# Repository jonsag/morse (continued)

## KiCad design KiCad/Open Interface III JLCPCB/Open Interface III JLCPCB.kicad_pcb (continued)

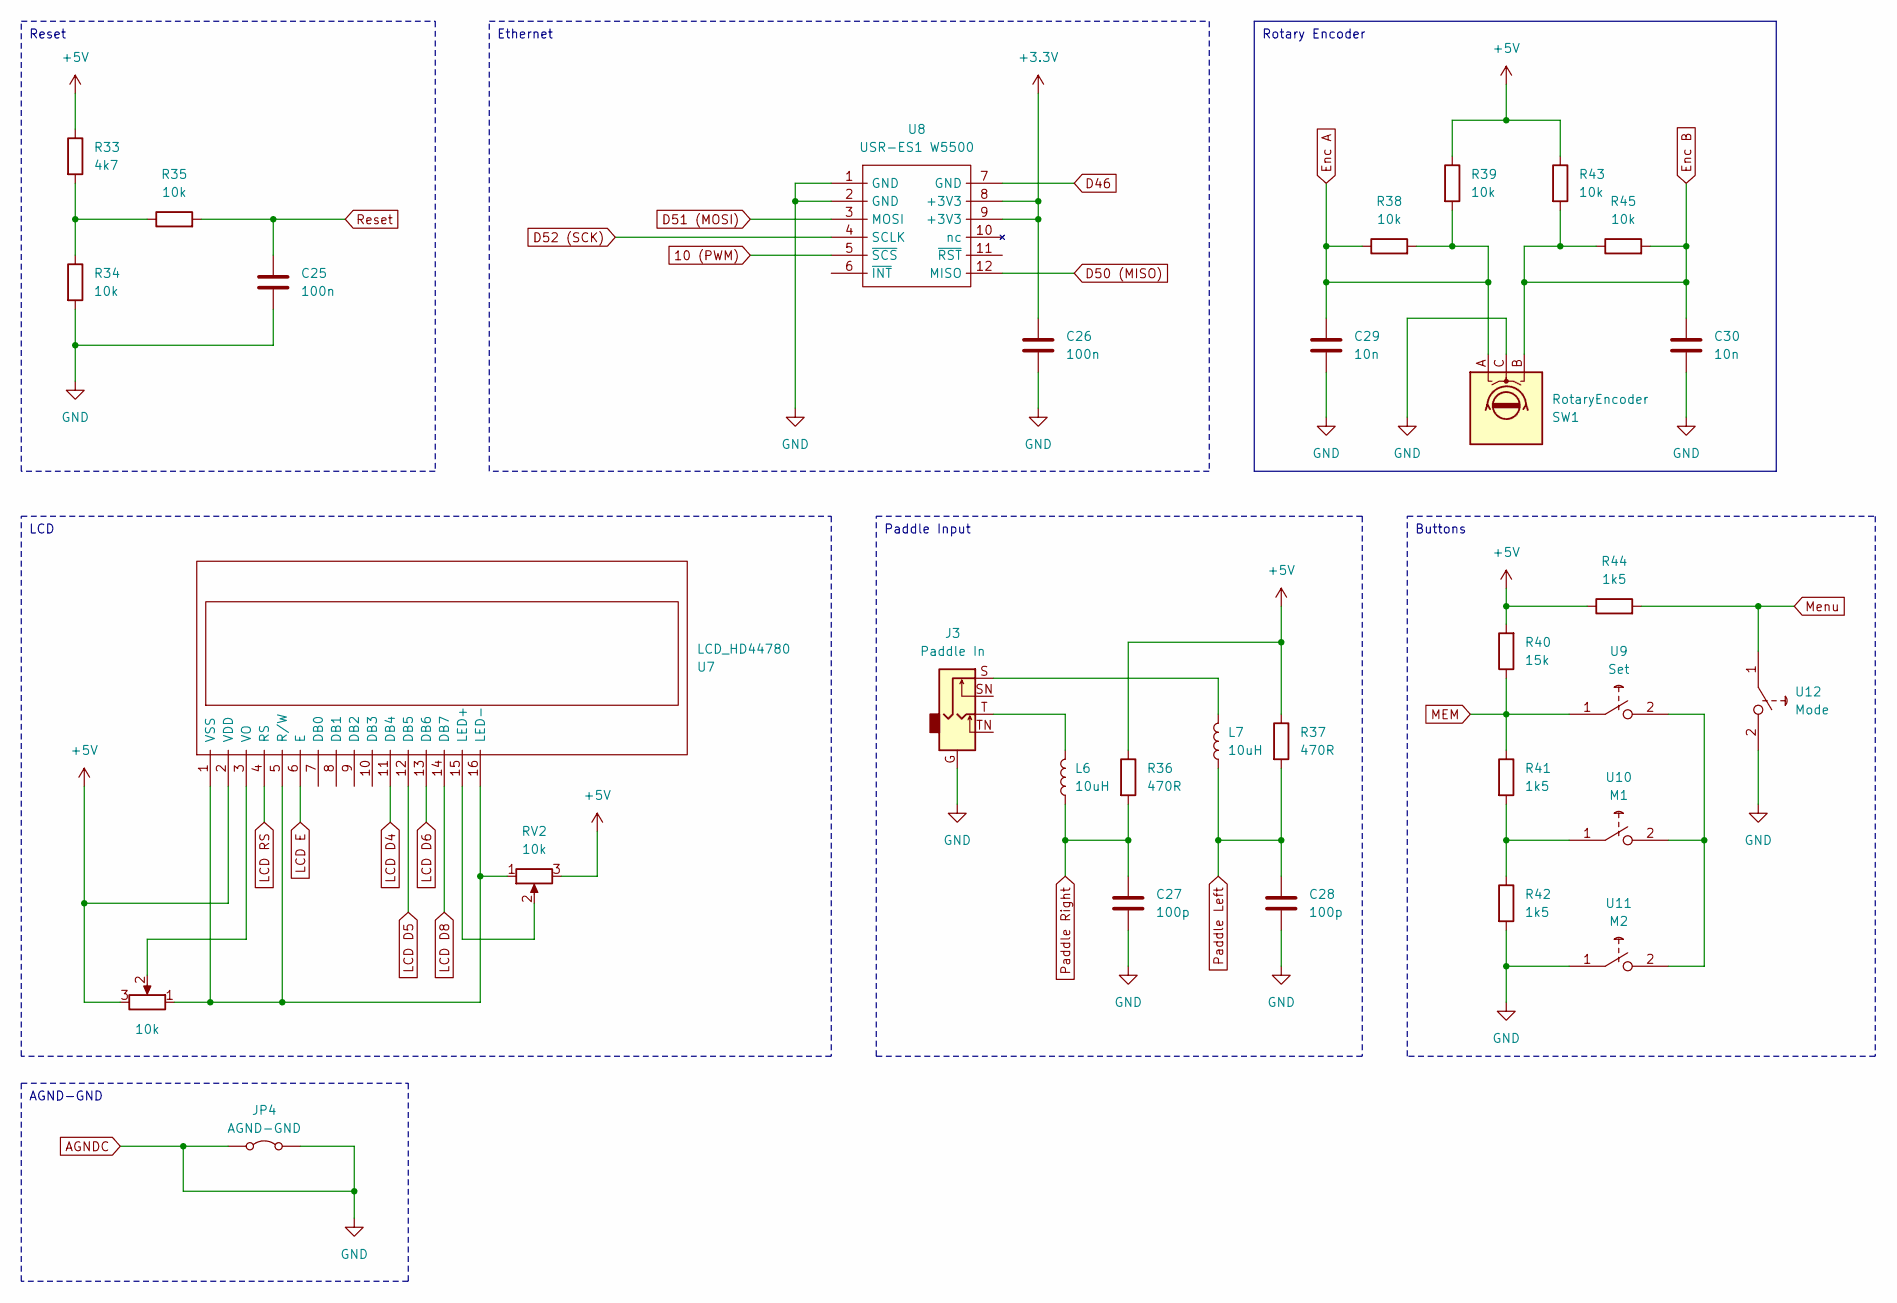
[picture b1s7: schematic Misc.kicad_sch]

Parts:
C25, C26: 100n; C_0201_0603Metric; MPN C1590
C27, C28: 100p; C_0201_0603Metric; MPN C1635
C29, C30: 10n; C_0201_0603Metric; MPN C1589
J3: Paddle In; 3,5mm Jack Panel Socket 3-pole Switch large
JP4: AGND-GND; PinHeader_1x02_P2.54mm_Vertical
L6, L7: 10uH; L_0201_0603Metric; MPN C1035
R33: 4k7; R_0201_0603Metric; MPN C23162
R34, R35, R38, R39, R43, R45: 10k; R_0201_0603Metric; MPN C15401
R36, R37: 470R; R_0201_0603Metric; MPN C23179
R40: 15k; R_0201_0603Metric; MPN C22809
R41, R42, R44: 1k5; R_0201_0603Metric; MPN C22843
RV1, RV2: 10k; 3-pin JST Potentiometer
SW1: RotaryEncoder; 3-pin JST Rotary Encoder
U7: LCD_HD44780; 2 x 6-pin JST LCD HD44780 Stacked
U8: USR-ES1 W5500
U9: Set; 2-pin JST Switch
U10: M1; 2-pin JST Switch
U11: M2; 2-pin JST Switch
U12: Mode; 2-pin JST Switch

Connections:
10 (PWM): U8.5 (~SCS); also elsewhere on the board
+3.3V: C26.1, U8.8 (+3V3), U8.9 (+3V3); also elsewhere on the board
+5V: R33.1, R36.1, R37.1, R39.1, R40.2, R43.1, R44.1, RV1.3, RV2.3, U7.2 (VDD); also elsewhere on the board
AGNDC: C25.2, C26.2, C27.2, C28.2, C29.2, C30.2, J3.G, JP4.1 (A), JP4.2 (B), R34.2, R42.2, SW1.C, U8.1 (GND), U8.2 (GND), U11.1 (Com), U12.2 (NO); also elsewhere on the board
D46: U8.7 (GND); also elsewhere on the board
D50 (MISO): U8.12 (MISO); also elsewhere on the board
D51 (MOSI): U8.3 (MOSI); also elsewhere on the board
D52 (SCK): U8.4 (SCLK); also elsewhere on the board
DTR: C25.1, R35.2; also elsewhere on the board
Enc A: C29.1, R38.1, R38.2, R39.2, SW1.A; also elsewhere on the board
Enc B: C30.1, R43.2, R45.1, R45.2, SW1.B
LCD D4: U7.11 (DB4); also elsewhere on the board
LCD D5: U7.12 (DB5); also elsewhere on the board
LCD D6: U7.13 (DB6); also elsewhere on the board
LCD D8: U7.14 (DB7)
LCD E: U7.6 (E); also elsewhere on the board
LCD RS: U7.4 (RS); also elsewhere on the board
MEM: R40.1, R41.1, U9.1 (Com)
Menu: R44.2, U12.1 (Com); also elsewhere on the board
unnamed: J3.S, L7.2
unnamed: J3.T, L6.2
unnamed: R33.2, R34.1, R35.1
unnamed: RV2.2, U7.15 (LED+)
unnamed: RV1.1, RV2.1, U7.1 (VSS), U7.5 (R/W), U7.16 (LED-)
unnamed: RV1.2, U7.3 (VO)
unnamed: R41.2, R42.1, U10.1 (Com)
unnamed: U9.2 (NO), U10.2 (NO), U11.2 (NO)
Paddle Left: C28.1, L7.1, R37.2; also elsewhere on the board
Paddle Right: C27.1, L6.1, R36.2; also elsewhere on the board

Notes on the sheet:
Paddle Input
Buttons
AGND-GND
Ethernet
LCD
Reset
Rotary Encoder

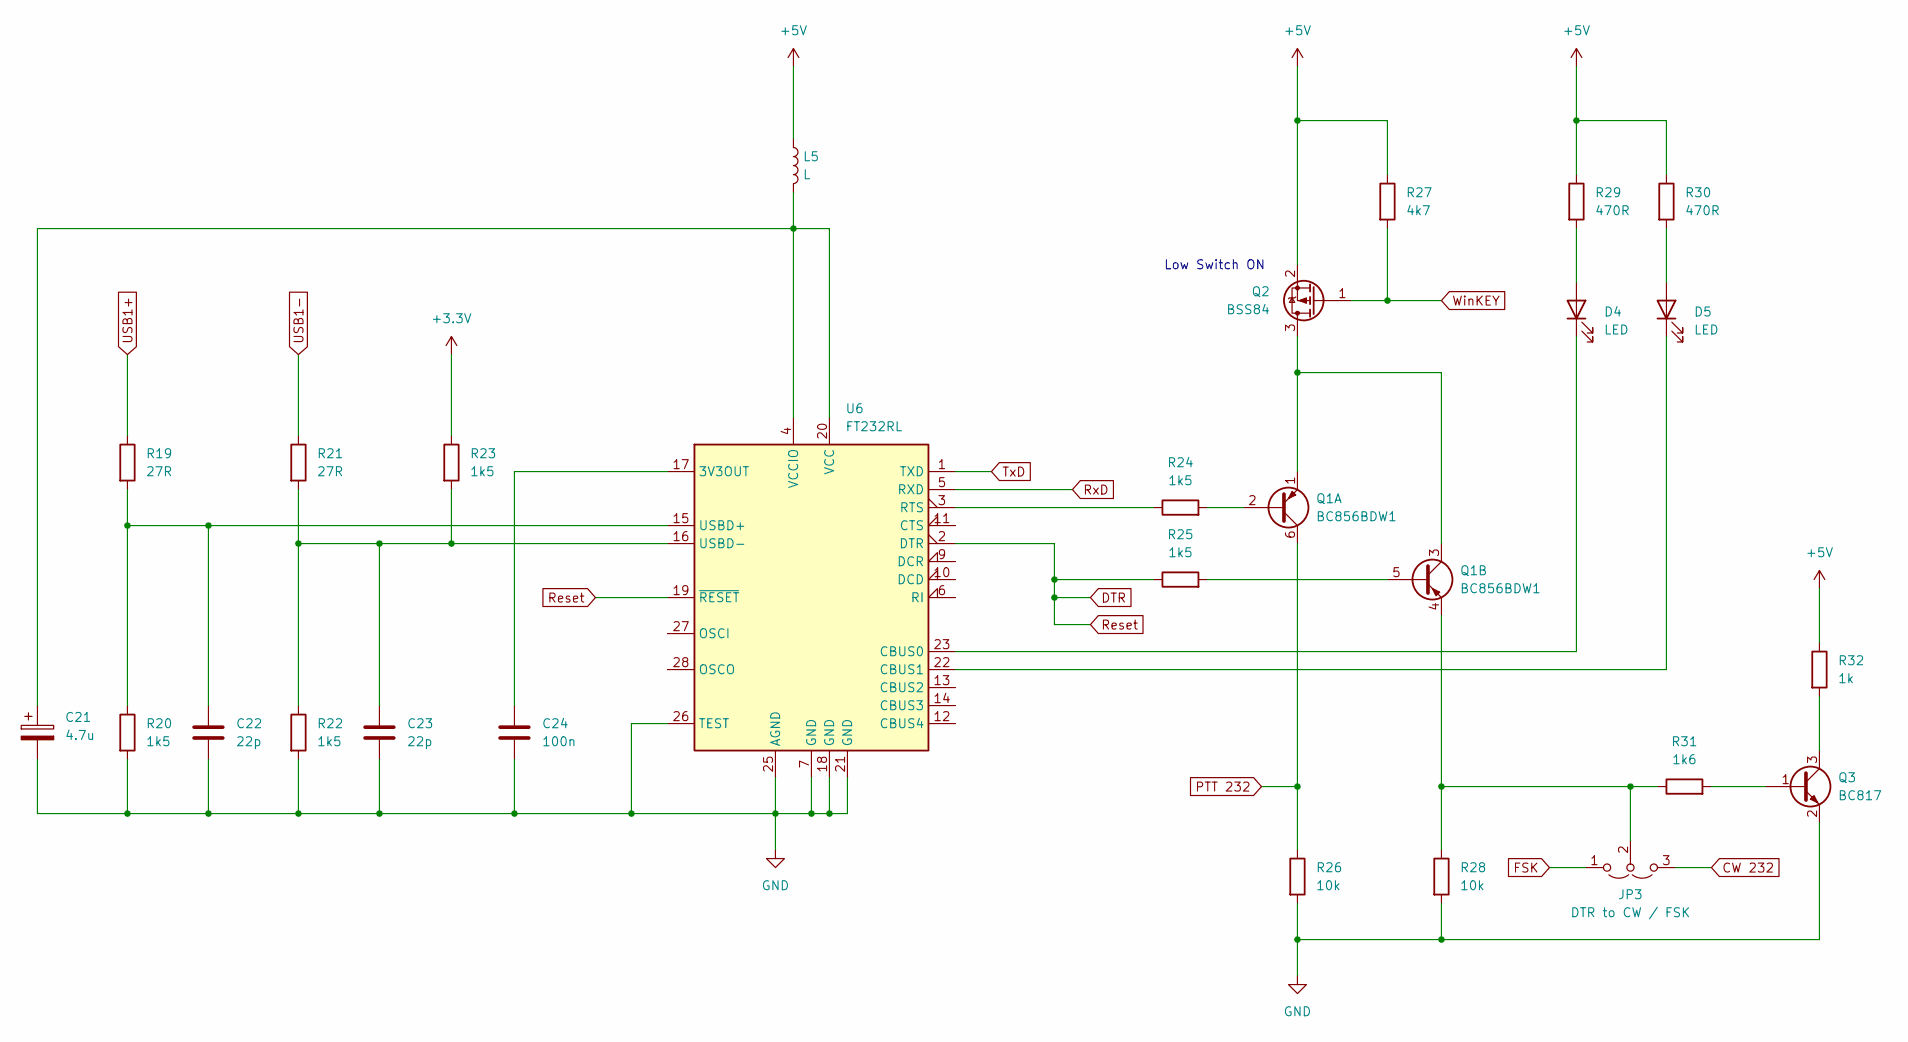
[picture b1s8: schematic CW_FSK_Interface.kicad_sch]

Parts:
C21: 4.7u; CP_Elec_5x5.4; MPN C4747957
C22, C23: 22p; C_0201_0603Metric; MPN C1653
C24: 100n; C_0201_0603Metric; MPN C1590
D4, D5: LED; 2-pin JST LED
JP3: DTR to CW / FSK; Jumper_1x03_P2.54mm_large
L5: L; L_1206_3216Metric_Pad1.22x1.90mm_HandSolder
Q1: BC856BDW1; SOT-363_SC-70-6; MPN C383196
Q2: BSS84; SOT-23; MPN C8492
Q3: BC817; SOT-23-3; MPN C2137
R19, R21: 27R; R_0201_0603Metric; MPN C25190
R20, R22, R23, R24, R25: 1k5; R_0201_0603Metric; MPN C22843
R26, R28: 10k; R_0201_0603Metric; MPN C15401
R27: 4k7; R_0201_0603Metric; MPN C23162
R29, R30: 470R; R_0201_0603Metric; MPN C23179
R31: 1k6; R_0201_0603Metric; MPN C22847
R32: 1k; R_0201_0603Metric; MPN C14676
U6: FT232RL; SSOP-28_5.3x10.2mm_P0.65mm

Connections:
+3.3V: R23.1; also elsewhere on the board
+5V: L5.1, Q2.2 (S), R27.1, R29.1, R30.1, R32.1; also elsewhere on the board
AGNDC: C21.2, C22.2, C23.2, C24.2, Q3.2 (E), R20.2, R22.2, R26.2, R28.2, U6.7 (GND), U6.18 (GND), U6.21 (GND), U6.25 (AGND), U6.26 (TEST); also elsewhere on the board
CW 232: JP3.3 (B); also elsewhere on the board
DTR: R25.1, U6.2 (DTR), U6.19 (~RESET); also elsewhere on the board
FSK: JP3.1 (A); also elsewhere on the board
unnamed: D4.2 (A), R29.2
unnamed: D4.1 (K), U6.23 (CBUS0)
unnamed: D5.2 (A), R30.2
unnamed: D5.1 (K), U6.22 (CBUS1)
unnamed: JP3.2 (C), Q1.4 (E2), R28.1, R31.1
unnamed: Q1.2 (B1), R24.2
unnamed: Q1.1 (E1), Q1.3 (C2), Q2.3 (D)
unnamed: Q1.5 (B2), R25.2
unnamed: Q3.1 (B), R31.2
unnamed: Q3.3 (C), R32.2
unnamed: C24.1, U6.17 (3V3OUT)
unnamed: R24.1, U6.3 (RTS)
unnamed: C22.1, R19.2, R20.1, U6.15 (USBD+)
unnamed: C23.1, R21.2, R22.1, R23.2, U6.16 (USBD-)
unnamed: C21.1, L5.2, U6.4 (VCCIO), U6.20 (VCC)
PTT 232: Q1.6 (C1), R26.1; also elsewhere on the board
RxD: U6.5 (RXD); also elsewhere on the board
TxD: U6.1 (TXD); also elsewhere on the board
USB1+: R19.1; also elsewhere on the board
USB1-: R21.1; also elsewhere on the board
WinKEY: Q2.1 (G), R27.2; also elsewhere on the board

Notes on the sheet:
Low Switch ON

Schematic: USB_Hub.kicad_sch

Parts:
C17, C18: 22p; C_0201_0603Metric; MPN C1653
C19, C20: 27p; C_0201_0603Metric; MPN C1656
R14, R15: 24R; R_0201_0603Metric; MPN C4198
R16, R17: 1k5; R_0201_0603Metric; MPN C22843
R18: 1M; R_0201_0603Metric; MPN C22935
U5: TUSB2046B; LQFP-32_7x7mm_P0.8mm
Y2: 6MHz; Crystal_SMD_HC49-SD; MPN C29835

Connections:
+3.3V: U5.3 (VCC), U5.10 (~OVRCUR1), U5.14 (~OVRCUR2), U5.18 (~OVRCUR3), U5.22 (~OVERCUR4), U5.25 (VCC), U5.26 (~EXTMEM); also elsewhere on the board
AGNDC: C17.2, C18.2, C19.2, C20.2, R16.2, U5.6 (EEDATA/~GANGED), U5.7 (GND), U5.8 (~BUSPWR), U5.27 (TSTPLL/48MCLK), U5.28 (GND), U5.31 (TSTMODE); also elsewhere on the board
DTR: U5.4 (~RESET); also elsewhere on the board
HUB+: R15.1
HUB-: R14.1
unnamed: C19.1, R17.1, R18.1, Y2.1
unnamed: C18.1, R15.2, U5.2 (DM0)
unnamed: C17.1, R14.2, R16.1, U5.1 (DP0)
unnamed: C20.1, R18.2, U5.30 (XTAL1), Y2.2
unnamed: R17.2, U5.29 (XTAL2)
USB1+: U5.12 (DP1); also elsewhere on the board
USB1-: U5.11 (DM1); also elsewhere on the board
USB2+: U5.16 (DP2); also elsewhere on the board
USB2-: U5.15 (DM2); also elsewhere on the board
USB3+: U5.20 (DP3); also elsewhere on the board
USB3-: U5.19 (DM3); also elsewhere on the board
USB4+: U5.24 (DP4); also elsewhere on the board
USB4-: U5.23 (DM4); also elsewhere on the board

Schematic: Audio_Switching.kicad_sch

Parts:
C83, C84, C85, C86: 4.7n; C_0201_0603Metric; MPN C1621
C87: 10u; CP_Elec_4x5.4; MPN C2029
D35, D36: 1N4148; D_SOD-523
J9: Mic In; 3,5mm Jack Panel Socket 3-pole Switch large
JP7: DC to Mic; PinHeader_1x02_P2.54mm_Vertical
K2, K3: G5V-1; Relay_SPDT_Omron_G5V-1
L28, L29, L30, L31: 10uH; L_0201_0603Metric; MPN C1035
Q5: BC817; SOT-23-3; MPN C2137
Q6: BC856B; SOT-23-3; MPN C85077
R83: 10k; R_0201_0603Metric; MPN C15401
R84, R85: 1k5; R_0201_0603Metric; MPN C22843
RV5: 10k; 3-pin JST Potentiometer
U24, U25: 2 x RCA Jack; pro-signal PSG01550 Dual 2× RCA Phono SocketRight Angle PCB

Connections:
+5V: D35.1 (K), D36.1 (K), K2.2, K3.2, R83.1; also elsewhere on the board
AFSK: R85.1; also elsewhere on the board
AGNDC: C83.2, C84.2, C85.2, C86.2, Q5.2 (E), Q6.3 (C), U24.1, U25.1; also elsewhere on the board
Interlock In: C84.1, L29.1; also elsewhere on the board
Mic Out: K3.5, K3.6; also elsewhere on the board
unnamed: D35.2 (A), K2.9, Q5.3 (C)
unnamed: D36.2 (A), K3.9, Q6.2 (E)
unnamed: C87.2, JP7.1 (A), K3.10
unnamed: C87.1, J9.T, JP7.2 (B)
unnamed: K2.1, RV5.3
unnamed: K3.1, RV5.2
unnamed: L28.1, U24.3
unnamed: L29.2, U25.2
unnamed: L30.2, U25.3
unnamed: L31.1, U24.2
unnamed: Q5.1 (B), R85.2
unnamed: Q6.1 (B), R84.2
PA PTT Out: C85.1, L30.1; also elsewhere on the board
PTT from Foot: C86.1, L31.2, R83.2, R84.1; also elsewhere on the board
SEQ Out: C83.1, L28.2; also elsewhere on the board
Tx Audio: K2.10
Tx Audio GND: J9.G, RV5.1; also elsewhere on the board
Tx Sound: K2.5, K2.6; also elsewhere on the board

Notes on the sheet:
Sequencer
Foot PTT
PA PTT
Interlock In

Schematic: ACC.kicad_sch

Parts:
J10: UART; PinHeader_1x03_P2.54mm_Vertical
J11: HDMI_A; HDMI_A_Kycon_KDMIX-SL1-NS-WS-B15_VerticalRightAngle

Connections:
+5V: J11.18 (+5V); also elsewhere on the board
A3: J11.12 (CK-); also elsewhere on the board
A4: J11.13 (CEC); also elsewhere on the board
A8: J11.14 (UTILITY); also elsewhere on the board
A9: J11.17 (GND); also elsewhere on the board
A11: J11.19 (HPD); also elsewhere on the board
AGNDC: J10.3, J11.2 (D2S), J11.SH; also elsewhere on the board
D5: J11.6 (D1-); also elsewhere on the board
D11: J11.9 (D0-); also elsewhere on the board
D12: J11.10 (CK+); also elsewhere on the board
D13: J11.5 (D1S); also elsewhere on the board
D30: J11.7 (D0+); also elsewhere on the board
D32: J11.8 (D0S); also elsewhere on the board
D38: J11.11 (CKS); also elsewhere on the board
D47: J11.4 (D1+); also elsewhere on the board
RxD3: J10.1, J11.1 (D2+); also elsewhere on the board
SCL: J11.15 (SCL); also elsewhere on the board
SDA: J11.16 (SDA); also elsewhere on the board
TxD3: J10.2, J11.3 (D2-); also elsewhere on the board

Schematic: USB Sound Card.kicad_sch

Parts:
C59, C62, C65, C66, C77, C79: 10u; CP_Elec_4x5.4; MPN C2029
C60, C61, C78, C80: 22p; C_0201_0603Metric; MPN C1653
C63: 100n; C_0201_0603Metric; MPN C1590
C64: 47u; CP_Elec_5x5.4; MPN C3337
C67, C71, C72, C75, C81, C82: 1u; CP_Elec_4x5.4; MPN C3348
C68, C74: 1n; C_0201_0603Metric; MPN C1588
C69, C73: 10u; C_0201_0603Metric; MPN C1691
C70: 68n; C_0201_0603Metric; MPN C31658
C76: 4.7u; CP_Elec_5x5.4; MPN C4747957
D31, D32, D33, D34: 1N4148; D_SOD-523
L27: L; L_1206_3216Metric_Pad1.22x1.90mm_HandSolder
Q4: BC817; SOT-23-3; MPN C2137
R67, R71: 27R; R_0201_0603Metric; MPN C25190
R68, R76, R77, R78, R82: 4k7; R_0201_0603Metric; MPN C23162
R69, R75: 100k; R_0201_0603Metric; MPN C14675
R70, R79: 470R; R_0201_0603Metric; MPN C23179
R72, R74: 15k; R_0201_0603Metric; MPN C22809
R73: 1k5; R_0201_0603Metric; MPN C22843
R80: 1k; R_0201_0603Metric; MPN C14676
R81: 1M; R_0201_0603Metric; MPN C22935
RV4: 10k log; 3-pin JST Potentiometer
T1, T2: Transformer_1P_1S; Audio Transformer Bourns SM-LP-5001; MPN C7503474
U20: Vol -; 2-pin JST Switch
U21: Vol +; 2-pin JST Switch
U22: Mute; 2-pin JST Switch
U23: PCM2904; SSOP-28_5.3x10.2mm_P0.65mm
Y3: 12 MHz; Crystal_SMD_HC49-SD

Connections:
+3.3V: R73.1; also elsewhere on the board
+5V: L27.1; also elsewhere on the board
AGNDC: C60.2, C61.2, C63.2, C64.2, C67.2, C71.2, C72.2, C75.2, C76.2, C77.2, C78.2, C80.2, C82.2, D32.1 (K), D34.2 (A), R70.2, R72.1, R74.1, R75.2, U23.4 (DGNDU), U23.11 (AGNDC), U23.18 (AGNDP), U23.22 (AGNDX), U23.24 (TEST0), U23.26 (DGND); also elsewhere on the board
unnamed: C63.1, R68.2
unnamed: C66.2, RV4.2
unnamed: C73.1, R79.2
unnamed: C79.2, C81.2, R82.2
unnamed: C59.2, C62.2, C65.2, D31.2 (A), D33.1 (K)
unnamed: D31.1 (K), D32.2 (A)
unnamed: D33.2 (A), D34.1 (K)
unnamed: C66.1, Q4.1 (B), R69.2, R75.1
unnamed: C59.1, Q4.3 (C), R68.1, R69.1
unnamed: C64.1, Q4.2 (E), R70.1
unnamed: RV4.1, T1.1 (AA)
unnamed: RV4.3, T1.2 (AB)
unnamed: C69.2, T1.4 (SB)
unnamed: C73.2, T2.1 (AA)
unnamed: C74.2, T2.2 (AB)
unnamed: R80.1, R82.1, T2.4 (SB)
unnamed: R76.2, U20.1 (Com)
unnamed: U20.2 (NO), U23.7 (HID2)
unnamed: R77.2, U21.1 (Com)
unnamed: U21.2 (NO), U23.6 (HID1)
unnamed: R78.2, U22.1 (Com)
unnamed: U22.2 (NO), U23.5 (HID0)
unnamed: R71.2, R73.2, R74.2, U23.1 (D+)
unnamed: R67.2, R72.2, U23.2 (D-)
unnamed: C67.1, U23.8 (SEL0), U23.9 (SEL1), U23.27 (VDDI)
unnamed: C82.1, L27.2, U23.3 (VBUS)
unnamed: C77.1, U23.10 (VCCCI)
unnamed: C75.1, U23.17 (VCCP1I)
unnamed: C72.1, U23.19 (VCCP2I)
unnamed: C71.1, U23.23 (VCCXI)
unnamed: C76.1, U23.14 (VCOM)
unnamed: C65.1, U23.12 (VINL)
unnamed: C62.1, U23.13 (VINR)
unnamed: C79.1, U23.16 (VOUTL)
unnamed: C81.1, U23.15 (VOUTR)
unnamed: C80.1, R81.2, U23.21 (XTI), Y3.2
unnamed: C78.1, R81.1, U23.20 (XTO), Y3.1
unnamed: R76.1, R77.1, R78.1, U23.28 (~SSPND)
Rx Audio: C68.1, C69.1
Rx Audio GND: C68.2, T1.3 (SA)
Tx Audio GND: C70.2, C74.1; also elsewhere on the board
Tx Sound: C70.1, R79.1; also elsewhere on the board
USB3+: C61.1, R71.1; also elsewhere on the board
USB3-: C60.1, R67.1; also elsewhere on the board
VGNDC: R80.2, T2.3 (SA)

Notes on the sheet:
Option

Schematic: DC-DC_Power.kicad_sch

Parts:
C36: 100u; CP_Elec_6.3x7.7; MPN C3338
C37, C38, C39, C42: 100n; C_0201_0603Metric; MPN C1590
C40, C41: 10u; CP_Elec_4x5.4; MPN C2029
C43: 1000u; CP_Elec_8x10.5; MPN C42851
D6, D7, D8: SK38; D_SMB; MPN C28646291
J7: Barrel_Jack_Switch; BarrelJack_Horizontal
L24, L25: 100uH; L_SXN_SMDRI124; MPN C10150
RV3: 18VDC; RV_Disc_D12mm_W3.9mm_P7.5mm
U15: LM2576HVS-5; TO-263-5_TabPin6; MPN LM2576HVS-5
U16: L78L33_SOT89; SOT-89-3; MPN C14170

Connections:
+3.3V: C41.1, C42.1, U16.1 (OUT); also elsewhere on the board
+5V: C37.1, C39.1, C40.1, C43.1, L25.2, U15.4 (FB), U16.3 (IN); also elsewhere on the board
AGNDC: C36.2, C37.2, C38.2, C39.2, C40.2, C41.2, C42.2, C43.2, D8.2 (A), J7.2, RV3.2, U15.3 (GND), U15.5 (~ON/OFF), U16.2 (GND); also elsewhere on the board
unnamed: D6.1 (K), D7.1 (K), L24.1
unnamed: D7.2 (A), J7.1
unnamed: D8.1 (K), L25.1, U15.2 (OUT)
Vin: C36.1, C38.1, L24.2, RV3.1, U15.1 (VIN); also elsewhere on the board
Vin TRX: D6.2 (A); also elsewhere on the board

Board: 2 copper layers, 302 parts (0 on the bottom side), 257 nets, no tracks yet.

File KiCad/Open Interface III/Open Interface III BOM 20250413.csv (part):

"Reference","Value","Datasheet","Footprint","Qty","DNP"
"C1,C4,C8,C17,C18,C22,C23,C31,C32,C33,C53,C54,C60,C61,C78,C80","22p","~","Capacitor_SMD:C_1206_3216Metric_Pad1.33x1.80mm_HandSolder","16",""
"C2,C3,C5,C9,C44,C45,C47,C49,C83,C84,C85,C86","4.7n","~","Capacitor_SMD:C_1206_3216Metric_Pad1.33x1.80mm_HandSolder","12",""
"C6,C7,C10,C11,C12,C13,C14,C15,C16,C24,C25,C26,C34,C35,C37,C38,C39,C42,C46,C48,C50,C52,C63","100n","~","Capacitor_SMD:C_1206_3216Metric_Pad1.33x1.80mm_HandSolder","23",""
"C19,C20","27p","~","Capacitor_SMD:C_1206_3216Metric_Pad1.33x1.80mm_HandSolder","2",""
"C21,C76","4.7u","~","Capacitor_SMD:CP_Elec_4x5.4","2",""
"C27,C28","100p","~","Capacitor_SMD:C_1206_3216Metric_Pad1.33x1.80mm_HandSolder","2",""
"C29,C30","10n","~","Capacitor_SMD:C_1206_3216Metric_Pad1.33x1.80mm_HandSolder","2",""
"C36","100u","~","Capacitor_SMD:CP_Elec_8x10","1",""
"C40,C41,C59,C62,C65,C66,C69,C73,C77,C79,C87","10u","~","-- mixed values --","11",""
"C43","1000u","~","Capacitor_SMD:CP_Elec_8x10.5","1",""
"C51,C55,C56,C57,C58,C67,C71,C72,C75,C81,C82","1u","~","Capacitor_SMD:CP_Elec_5x5.4","11",""
"C64","47u","~","Capacitor_SMD:CP_Elec_6.3x5.8","1",""
"C68,C74","1n","~","Capacitor_SMD:C_1206_3216Metric_Pad1.33x1.80mm_HandSolder","2",""
"C70","68n","~","Capacitor_SMD:C_1206_3216Metric_Pad1.33x1.80mm_HandSolder","1",""
"D1,D2,D3,D9,D10,D11,D12,D13,D14,D15,D16,D17,D18,D22,D25,D30,D31,D32,D33,D34,D35,D36","1N4148","https://assets.nexperia.com/documents/data-sheet/1N4148_1N4448.pdf","Diode_SMD:D_SOD-523","22",""
"D4,D5","LED","~","MyFootprints:2-pin JST LED","2",""
"D6,D7,D8","SK38","https://diotec.com/request/datasheet/sk32.pdf","Diode_SMD:D_SMB","3",""
"D19,D20","Orange","~","MyFootprints:2-pin JST LED","2",""
"D21,D23,D24","Green","~","MyFootprints:2-pin JST LED","3",""
"D26,D27,D28,D29","D_Zener","~","Package_TO_SOT_SMD:SOT-23_Handsoldering","4",""
"J1","ICSP","~","MyFootprints:2x3_ISP_header","1",""
"J2","USB_B","~","MyFootprints:USB_B_OST_USB-B1HSxx_Horizontal","1",""
"J3","Paddle In","~","MyFootprints:3,5mm Jack Panel Socket 3-pole Switch large","1",""
"J4","USB Internal Conn","~","Connector_PinHeader_2.54mm:PinHeader_2x02_P2.54mm_Vertical","1",""
"J5","DB25_Receptacle_MountingHoles","~","Connector_Dsub:DSUB-25_Female_Horizontal_P2.77x2.84mm_EdgePinOffset4.94mm_Housed_MountingHolesOffset4.94mm","1",""
"J6","Micro_SD_Card_Det2","https://www.hirose.com/en/product/document?clcode=&productna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","Connector_Card:microSD_HC_Hirose_DM3AT-SF-PEJM5","1",""
"J7","Barrel_Jack_Switch","~","MyFootprints:BarrelJack_Horizontal","1",""
"J8","Conn_02x04_Odd_Even","~","Connector_PinHeader_2.54mm:PinHeader_2x04_P2.54mm_Vertical","1",""
"J9","Mic In","~","MyFootprints:3,5mm Jack Panel Socket 3-pole Switch large","1",""
"J10","UART","~","Connector_PinHeader_2.54mm:PinHeader_1x03_P2.54mm_Vertical","1",""
"J11","HDMI_A","https://en.wikipedia.org/wiki/HDMI","MyFootprints:HDMI_A_Kycon_KDMIX-SL1-NS-WS-B15_VerticalRightAngle","1",""
"JP1","Self Reset On","~","Connector_PinHeader_2.54mm:PinHeader_1x02_P2.54mm_Vertical","1",""
"JP2","Auro Reset On","~","Connector_PinHeader_2.54mm:PinHeader_1x02_P2.54mm_Vertical","1",""
"JP4","AGND-GND","~","Connector_PinHeader_2.54mm:PinHeader_1x02_P2.54mm_Vertical","1",""
"JP7","DC to Mic","~","Connector_PinHeader_2.54mm:PinHeader_1x02_P2.54mm_Vertical","1",""
"K1,K2,K3","G5V-1","http://omronfs.omron.com/en_US/ecb/products/pdf/en-g5v_1.pdf","Relay_THT:Relay_SPDT_Omron_G5V-1","3",""
"L1,L4,L6,L7,L8,L11,L12,L13,L14,L15,L16,L17,L19,L20,L21,L23,L28,L29,L30,L31","10uH","~","Inductor_SMD:L_1206_3216Metric_Pad1.22x1.90mm_HandSolder","20",""
"L2,L3,L5,L9,L10,L18,L22,L26,L27","L","~","Inductor_SMD:L_1206_3216Metric_Pad1.22x1.90mm_HandSolder","9",""
"L24,L25","100uH","~","Inductor_SMD:L_1206_3216Metric_Pad1.22x1.90mm_HandSolder","2",""
"Q1","BC856BDW1","http://www.onsemi.com/pub_link/Collateral/BC856BDW1T1-D.PDF","Package_TO_SOT_SMD:SOT-363_SC-70-6_Handsoldering","1",""
"Q2","BSS84","http://assets.nexperia.com/documents/data-sheet/BSS84.pdf","Package_TO_SOT_SMD:SOT-23","1",""
"Q3,Q4,Q5","BC817","https://www.onsemi.com/pub/Collateral/BC818-D.pdf","Package_TO_SOT_SMD:SOT-23-3","3",""
"Q6","BC856B","https://www.onsemi.com/pub/Collateral/BC860-D.pdf","Package_TO_SOT_SMD:SOT-23-3","1",""
"R1,R3,R4,R5,R65,R66","220R","~","Resistor_SMD:R_1206_3216Metric_Pad1.30x1.75mm_HandSolder","6",""
"R2,R18,R81","1M","~","Resistor_SMD:R_1206_3216Metric_Pad1.30x1.75mm_HandSolder","3",""
"R6,R11,R26,R28,R34,R35,R38,R39,R43,R45,R83,RV1,RV2,RV5","10k","~","-- mixed values --","14",""
"R7,R40,R50,R57,R58,R72,R74","15k","~","Resistor_SMD:R_1206_3216Metric_Pad1.30x1.75mm_HandSolder","7",""
"R8,R9,R10,R16,R17,R20,R22,R23,R24,R25,R41,R42,R44,R48,R49,R51,R56,R73,R84,R85","1k5","~","Resistor_SMD:R_1206_3216Metric_Pad1.30x1.75mm_HandSolder","20",""
"R12,R13,R14,R15","24R","~","Resistor_SMD:R_1206_3216Metric_Pad1.30x1.75mm_HandSolder","4",""
"R19,R21,R46,R47,R59,R60,R67,R71","27R","~","Resistor_SMD:R_1206_3216Metric_Pad1.30x1.75mm_HandSolder","8",""
"R27,R33,R63,R68,R76,R77,R78,R82","4k7","~","Resistor_SMD:R_1206_3216Metric_Pad1.30x1.75mm_HandSolder","8",""
"R29,R30,R36,R37,R53,R54,R55,R61,R62,R70,R79","470R","~","Resistor_SMD:R_1206_3216Metric_Pad1.30x1.75mm_HandSolder","11",""
"R31","1k6","~","Resistor_SMD:R_1206_3216Metric_Pad1.30x1.75mm_HandSolder","1",""
"R32,R64,R80","1k","~","Resistor_SMD:R_1206_3216Metric_Pad1.30x1.75mm_HandSolder","3",""
"R52,R69,R75","100k","~","Resistor_SMD:R_1206_3216Metric_Pad1.30x1.75mm_HandSolder","3",""
"RV3","18VDC","~","Varistor:RV_Disc_D12mm_W3.9mm_P7.5mm","1",""
"RV4","10k log","~","MyFootprints:3-pin JST Potentiometer","1",""
"SW1","RotaryEncoder","~","MyFootprints:3-pin JST Rotary Encoder","1",""
"T1,T2","Transformer_1P_1S","~","MyFootprints:Audio Transformer Bourns SM-LP-5001","2",""
"U1","Reset","","MyFootprints:2-pin JST Switch","1",""
"U2","ATmega2560-16A","http://ww1.microchip.com/downloads/en/DeviceDoc/Atmel-2549-8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","Package_QFP:TQFP-100_14x14mm_P0.5mm","1",""
"U3","NUP4202","http://www.onsemi.com/pub_link/Collateral/NUP4202W1-D.PDF","Package_TO_SOT_SMD:SOT-363_SC-70-6","1",""
"U4","ADUM4160","https://www.analog.com/media/en/technical-documentation/data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","Package_SO:SOIC-16W_7.5x10.3mm_P1.27mm","1",""
"U5","TUSB2046B","http://www.ti.com/lit/ds/symlink/tusb2036.pdf","Package_QFP:LQFP-32_7x7mm_P0.8mm","1",""
"U6,U18","FT232RL","https://www.ftdichip.com/Support/Documents/DataSheets/ICs/DS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","Package_SO:SSOP-28_5.3x10.2mm_P0.65mm","2",""
"U7","LCD_HD44780","","MyFootprints:2 x 6-pin JST LCD HD44780 Stacked","1",""
"U8","USR-ES1 W5500","https://www.pusr.com/download/ES1/USR-ES1-EN-V1.0.pdf","MyFootprints:USR-ES1 W5500","1",""
"U9","Set","","MyFootprints:2-pin JST Switch","1",""
"U10","M1","","MyFootprints:2-pin JST Switch","1",""
"U11","M2","","MyFootprints:2-pin JST Switch","1",""
"U12","Mode","","MyFootprints:2-pin JST Switch","1",""
"U13,U14","LSF0102","https://www.ti.com/lit/ds/symlink/lsf0102.pdf?ts=17443809144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","Package_TO_SOT_SMD:SOT-23W_Handsoldering","2",""
"U15","LM2576HVS-5","http://www.ti.com/lit/ds/symlink/lm2576.pdf","Package_TO_SOT_SMD:TO-263-5_TabPin3","1",""
"U16","L78L33_SOT89","http://www.st.com/content/ccc/resource/technical/document/da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","Package_TO_SOT_SMD:SOT-89-3_Handsoldering","1",""
"U17","ULN2803A","http://www.ti.com/lit/ds/symlink/uln2803a.pdf","MyFootprints:DIP-18_W7.62mm w socket","1",""
"U19","MAX232","http://www.ti.com/lit/ds/symlink/max232.pdf","Package_SO:SOIC-16_3.9x9.9mm_P1.27mm","1",""
"U20","Vol -","","MyFootprints:2-pin JST Switch","1",""
"U21","Vol +","","MyFootprints:2-pin JST Switch","1",""
"U22","Mute","","MyFootprints:2-pin JST Switch","1",""
"U23","PCM2904","https://www.ti.com/lit/ds/symlink/pcm2904.pdf?ts=17444580872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","Package_SO:SSOP-28_5.3x10.2mm_P0.65mm","1",""
"U24,U25","2 x RCA Jack","","MyFootprints:pro-signal PSG01550 Dual 2× RCA Phono SocketRight Angle PCB","2",""
"Y1","16MHz","~","Crystal:Crystal_SMD_HC49-SD","1",""
"Y2","6MHz","~","Crystal:Crystal_SMD_HC49-SD","1",""
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
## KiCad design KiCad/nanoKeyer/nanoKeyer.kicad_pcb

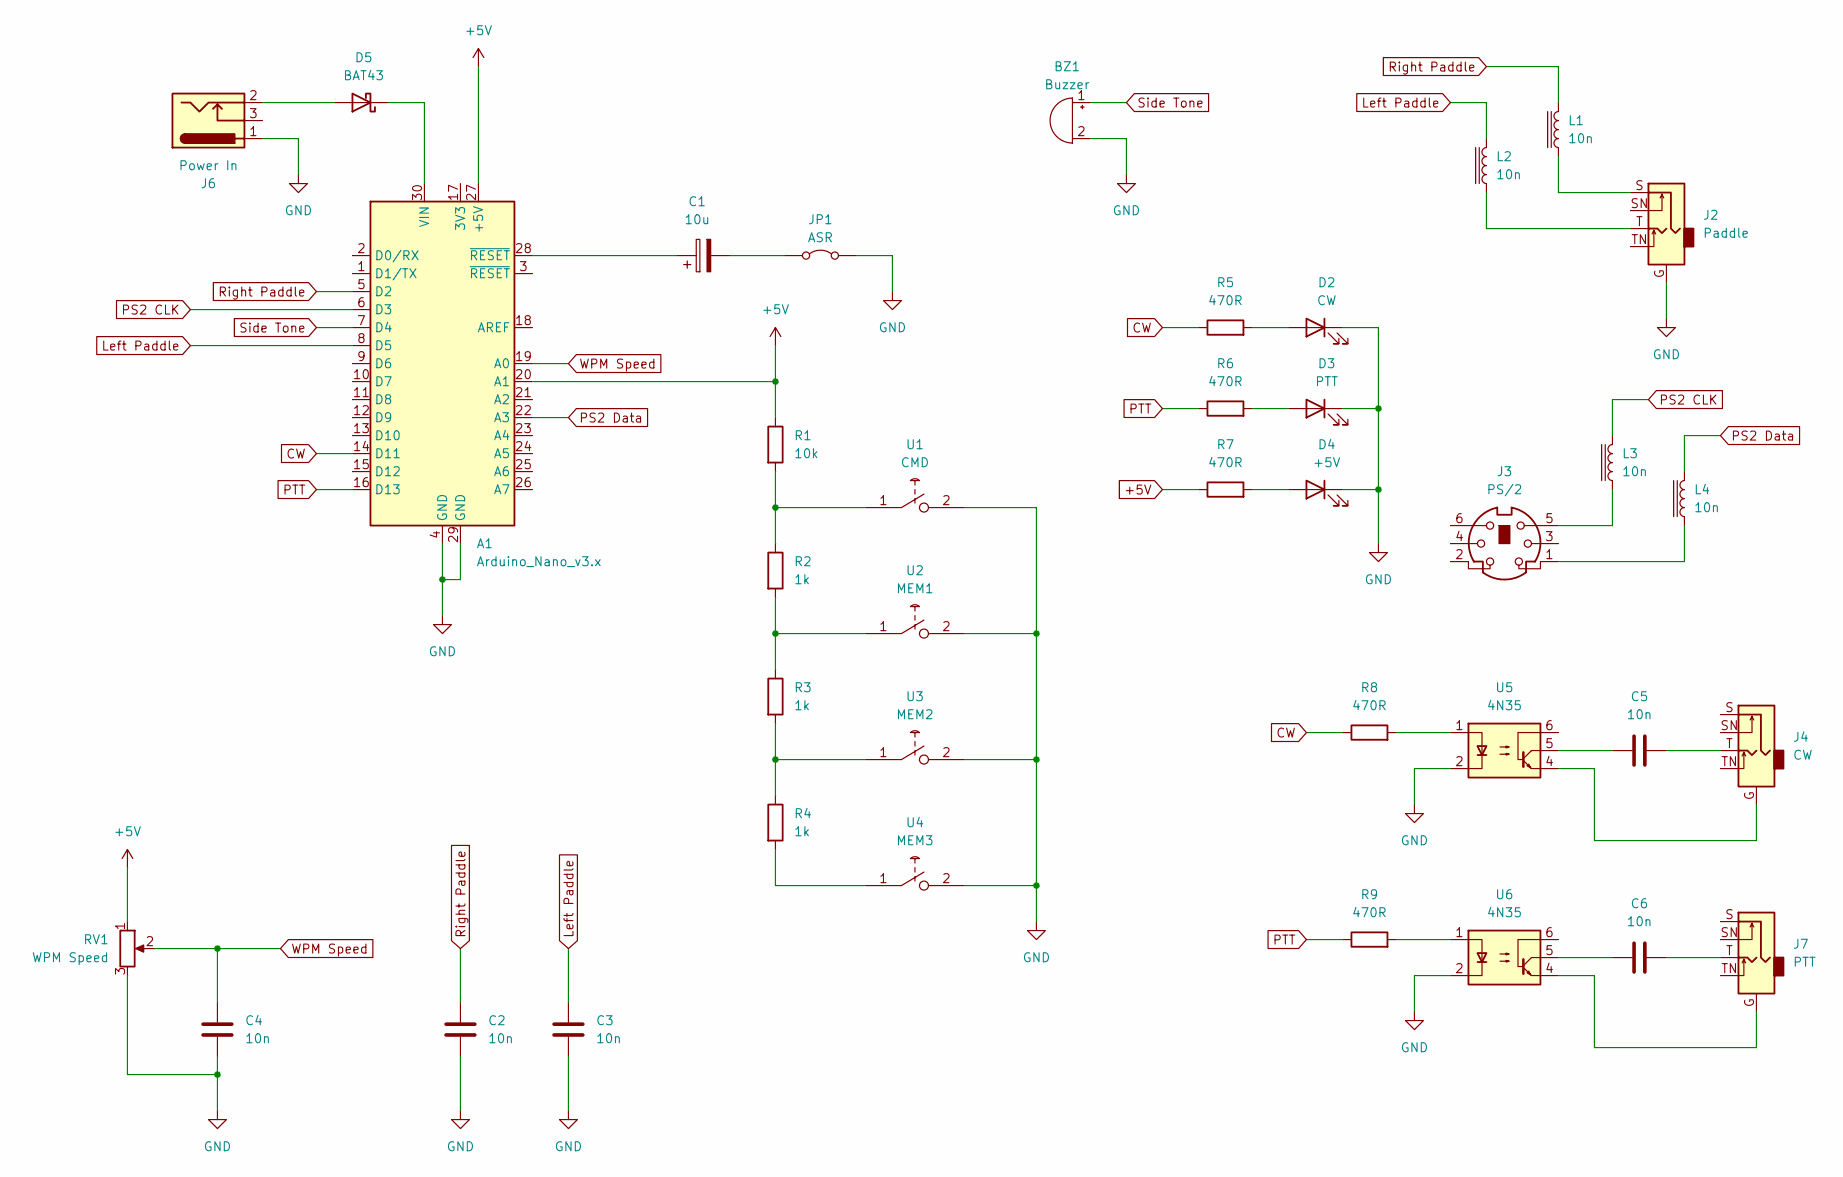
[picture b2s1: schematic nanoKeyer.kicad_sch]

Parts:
A1: Arduino_Nano_v3.x; ArduinoNano
BZ1: Buzzer; Passive Piezo Buzzer large
C1: 10u; CP_Radial_D5.0mm_P2.00mm_larger
C2, C3, C4, C5, C6: 10n; C_Disc_D3.0mm_W1.6mm_P2.50mm_larg
D2: CW; 2-pin JST LED
D3: PTT; 2-pin JST LED
D4: +5V; 2-pin JST LED
D5: BAT43; D_DO-35_SOD27_P7.62mm_Horizontal
J2: Paddle; 3,5mm Jack Panel Socket 3-pole Switch large
J3: PS/2; PS2 MINI-DIN-6-FULL-SHIELD
J4: CW; 3,5mm Jack Panel Socket 3-pole Switch large
J6: Power In; BarrelJack_Horizontal
J7: PTT; 3,5mm Jack Panel Socket 3-pole Switch large
JP1: ASR; Jumper_1x02_P2.54mm_large
L1, L2, L3, L4: 10n; L_Axial_L9.5mm_D4.0mm_P12.70mm_Horizontal_Fastron_SMCC_large
R1: 10k; R_Axial_DIN0207_L6.3mm_D2.5mm_P10.16mm_Horizontal_large
R2, R3, R4: 1k; R_Axial_DIN0207_L6.3mm_D2.5mm_P10.16mm_Horizontal_large
R5, R6, R7, R8, R9: 470R; R_Axial_DIN0207_L6.3mm_D2.5mm_P10.16mm_Horizontal_large
RV1: WPM Speed; 3-pin JST Potentiometer
U1: CMD; 2-pin JST Switch
U2: MEM1; 2-pin JST Switch
U3: MEM2; 2-pin JST Switch
U4: MEM3; 2-pin JST Switch
U5, U6: 4N35; DIP-6_W7.62mm

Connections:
+5V: A1.20 (A1), A1.27 (+5V), R1.1, R7.1, RV1.1
CW: A1.14 (D11), R5.1, R8.1
GND: A1.4 (GND), A1.29 (GND), BZ1.2 (-), C2.2, C3.2, C4.2, D2.1 (K), D3.1 (K), D4.1 (K), J2.G, J6.1, JP1.2 (B), RV1.3, U1.2 (NO), U2.2 (NO), U3.2 (NO), U4.2 (NO), U5.2, U6.2
Left Paddle: A1.8 (D5), C3.1, L2.1
unnamed: A1.30 (VIN), D5.1 (K)
unnamed: A1.28 (~RESET), C1.1
unnamed: C5.1, U5.5
unnamed: C5.2, J4.T
unnamed: C6.1, U6.5
unnamed: C6.2, J7.T
unnamed: D2.2 (A), R5.2
unnamed: D3.2 (A), R6.2
unnamed: D4.2 (A), R7.2
unnamed: D5.2 (A), J6.2
unnamed: J2.S, L1.1
unnamed: J2.T, L2.2
unnamed: J3.1, L4.2
unnamed: J3.5, L3.2
unnamed: J4.G, U5.4
unnamed: J7.G, U6.4
unnamed: C1.2, JP1.1 (A)
unnamed: R8.2, U5.1
unnamed: R9.2, U6.1
unnamed: R1.2, R2.1, U1.1 (Com)
unnamed: R2.2, R3.1, U2.1 (Com)
unnamed: R3.2, R4.1, U3.1 (Com)
unnamed: R4.2, U4.1 (Com)
PS2 CLK: A1.6 (D3), L3.1
PS2 Data: A1.22 (A3), L4.1
PTT: A1.16 (D13), R6.1, R9.1
Right Paddle: A1.5 (D2), C2.1, L1.2
Side Tone: A1.7 (D4), BZ1.1 (+)
WPM Speed: A1.19 (A0), C4.1, RV1.2

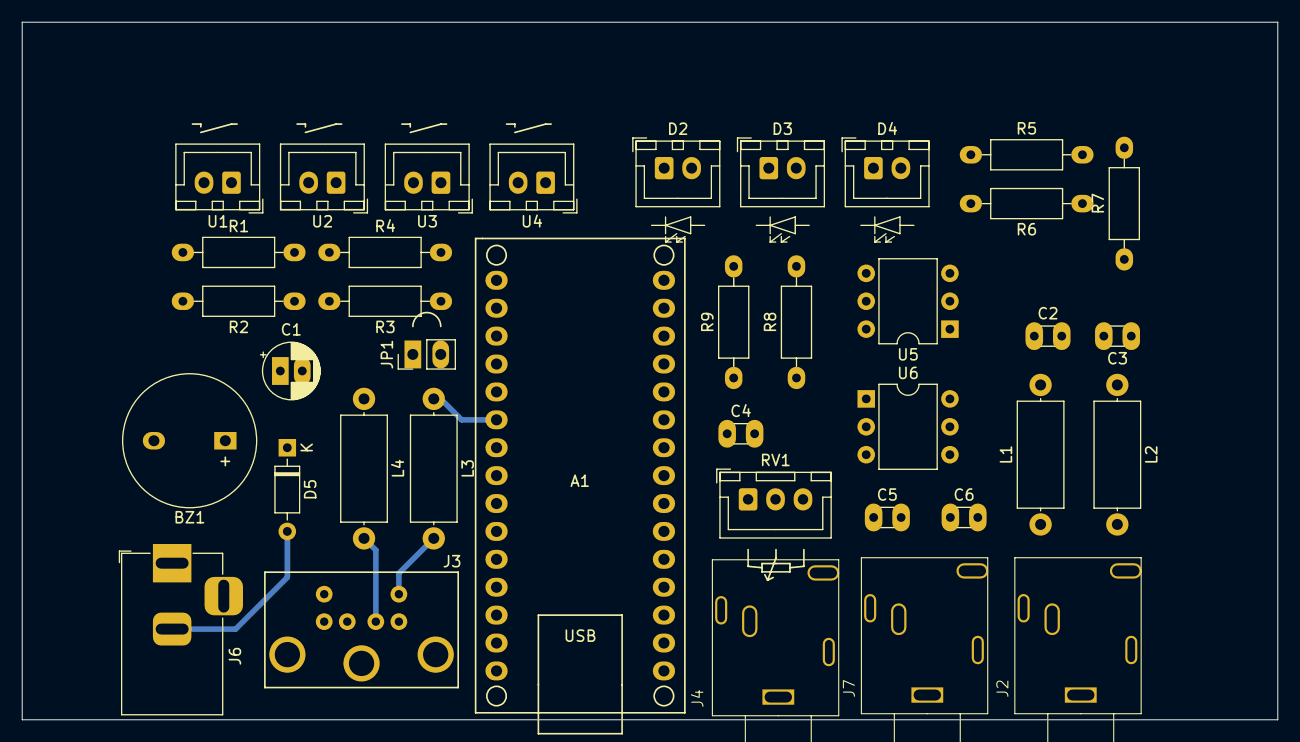
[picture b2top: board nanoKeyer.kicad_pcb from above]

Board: 2 copper layers, 114.3 x 63.5 mm, 38 parts (0 on the bottom side), 33 nets.

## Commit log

2025-04-11 Open Interface III
2025-04-11 nanoKeyer
2025-04-12 OI III Schematics 0.1
2025-04-12 OI III PCB 0.1
2025-04-13 PCB 0.1, BOM
2025-04-13 JLCPCB work in progress
